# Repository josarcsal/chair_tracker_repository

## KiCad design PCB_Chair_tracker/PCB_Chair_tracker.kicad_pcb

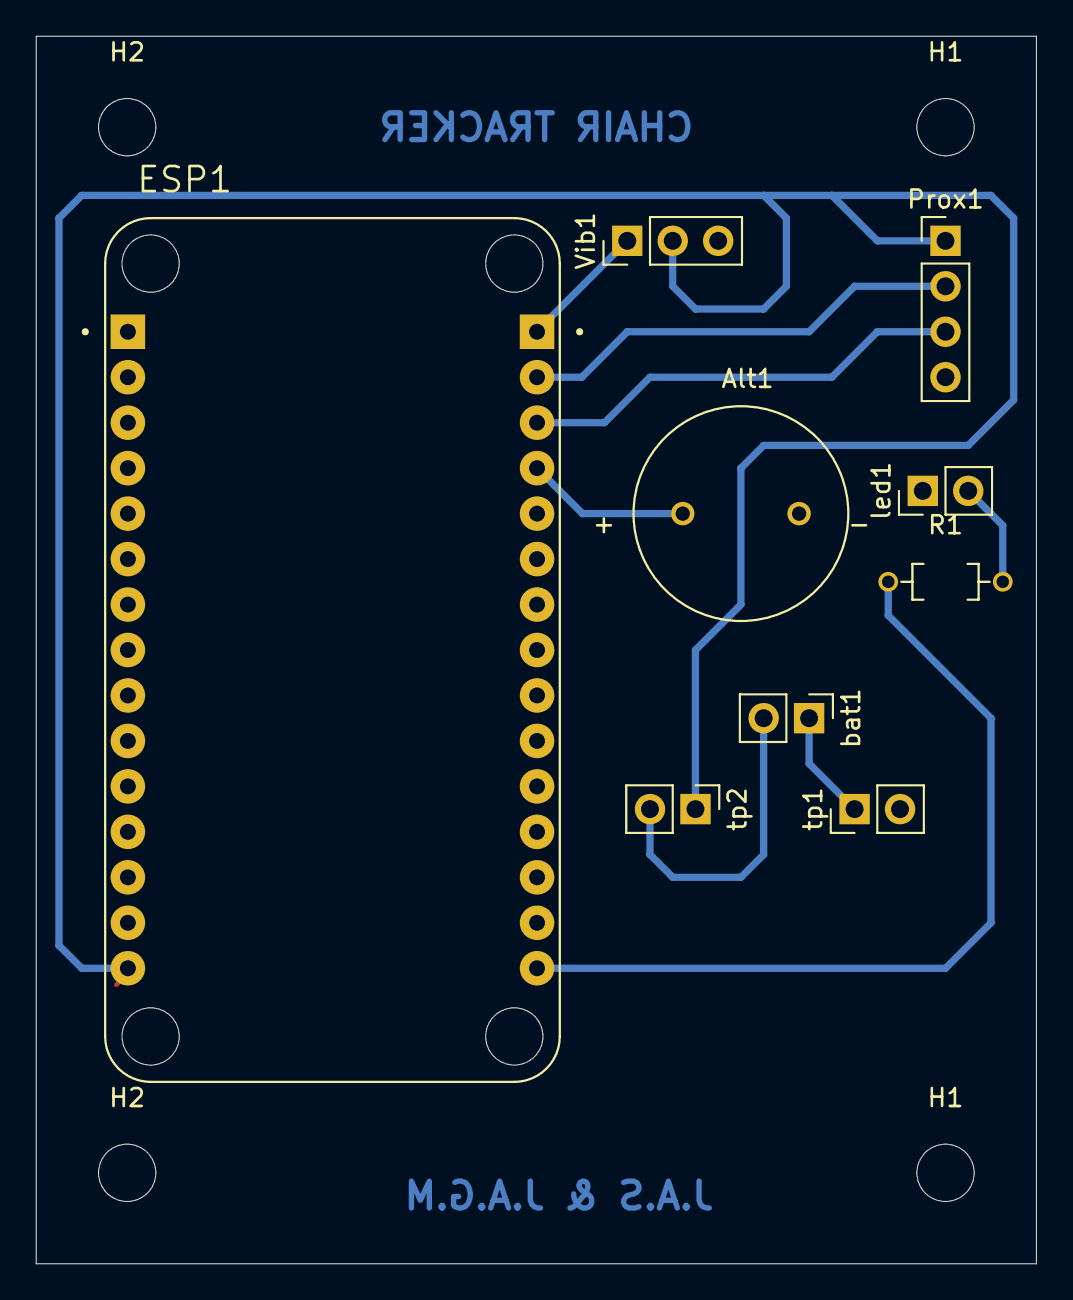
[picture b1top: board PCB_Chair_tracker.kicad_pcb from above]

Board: 2 copper layers, 55.9 x 68.6 mm, 13 parts (0 on the bottom side), 10 nets.

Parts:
Alt1: CEM-1203(42); CUI_CEM-1203(42)
ESP1: 113990105; SEEED_113990105
H1, H1#2, H2, H2#2: MountingHole; MountingHole_3.2mm_M3
Prox1: Conn_01x04_Male; PinHeader_1x04_P2.54mm_Vertical
R1: 1614977-1; RESAD640W45L370D200
Vib1: Conn_01x03_Male; PinHeader_1x03_P2.54mm_Vertical
bat1: Conn_01x02_Male; PinHeader_1x02_P2.54mm_Vertical
led1: Conn_01x02_Male; PinHeader_1x02_P2.54mm_Vertical
tp1, tp2: Conn_01x02_Male; PinHeader_1x02_P2.54mm_Vertical

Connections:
/3V3: ESP1.J2_15, R1.1
/ALARMA_PIN: Alt1.P, ESP1.J2_4
/B+: bat1.2, tp2.2
/B-: bat1.1, tp1.1
/ECHO_PIN: ESP1.J2_3, Prox1.3
/GND: Alt1.N, ESP1.J2_14, Prox1.4, Vib1.3, led1.1, tp1.2
/TRIGGER_PIN: ESP1.J2_2, Prox1.2
/VIBRADOR_PIN: ESP1.J2_1, Vib1.1
/VIN: ESP1.J1_15, Prox1.1, Vib1.2, tp2.1
unnamed: R1.2, led1.2

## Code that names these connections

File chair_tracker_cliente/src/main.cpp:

#include <Arduino.h>
#include <PubSubClient.h>
#include <Ethernet.h>
#include <ESP8266WiFi.h>
#include <ArduinoHttpClient.h>
#include <ArduinoJson.h>
#include <NewPing.h>
#include <ListLib.h>
#include <NTPClient.h>
#include "WiFiUdp.h"
#include <TimeLib.h>

#include "request.h"
#include "Hash.h"
#include "alarma.h"

#include "WiFiManager.h"      
#include <DNSServer.h>
#include <ESP8266WebServer.h>
#include <WiFiManager.h>        

//Obtener hora
WiFiUDP ntpUDP;
NTPClient timeClient(ntpUDP, "europe.pool.ntp.org", 7200);

//Sensor proximidad
#define TRIGGER_PIN D1
#define ECHO_PIN D2
#define MAX_DISTANCE 200 // Distancia máxima

NewPing sonar(TRIGGER_PIN, ECHO_PIN, MAX_DISTANCE);

//Alarma y vibrador
#define ALARMA_PIN D3
#define VIBRADOR_PIN D0

//Funciones mqtt
void callback(char *topic, byte *payload, unsigned int length);
void reconnect();

//Wifi
WiFiManager wm;
char server[40] = "0.0.0.0";
char http_port[6]  = "8084";
char mqtt_port[6]  = "1883";
WiFiManagerParameter custom_server("server", "Server IP", server, 40);
WiFiManagerParameter custom_http_port("http_port", "API Port", http_port, 6);
WiFiManagerParameter custom_mqtt_port("mqtt_port", "MQTT Port", mqtt_port, 6);

const char *mqttUser = "root";
const char *mqttPassword = "root";

WiFiClient espClient;
PubSubClient mqttClient(espClient);
HttpClient httpClient = HttpClient(espClient, server, atoi(http_port));

//Obtiene mac y realiza hash con algoritmo sha1 para mayor seguridad
String macEsp = sha1(WiFi.macAddress());
String hashMac = macEsp.substring(0,10);

//Gestion alarmas
String proxima;
int wifiFlag = 0;
int alarmaActiva = 0;
int inicioAlarma = 0;
int distanciaAnterior = 50;
int levantado = 10;
int marcaTiempo1;
int marcaTiempo2;
int contadorLevantado;
int contadorSentado;
int ciclosTrabajo;
int ciclosDescanso;

void setup()
{
  Serial.begin(9600);

  wm.resetSettings();
  
  //WIFI
  delay(3000);
  // Serial.println("Setup mode...");
  //wifiManager.resetSettings();
 
  wm.addParameter(&custom_server);
  wm.addParameter(&custom_mqtt_port);
  wm.addParameter(&custom_http_port);

  wm.setConfigPortalBlocking(false);

  if(wm.autoConnect("ChairTrackerAP"))
  {
    //if you get here you have connected to the WiFi
    Serial.println("connected...yeey :)");
  }
  else 
  {
    Serial.println("non blocking config portal running");
  }
  wm.startConfigPortal("ChairTrackerAP");

  Serial.print("Hash MAC: ");
  Serial.println(hashMac);
  
  //Alarma y vibrador
  pinMode(ALARMA_PIN, OUTPUT);
  pinMode(VIBRADOR_PIN, OUTPUT);
}

void loop()
{
  wm.process();
  if(WiFi.isConnected()){
    strcpy(server, custom_server.getValue());
    strcpy(http_port, custom_http_port.getValue());
    strcpy(mqtt_port, custom_mqtt_port.getValue());

    if(wifiFlag == 0){ 
      //MQTT
      mqttClient.setServer(server, atoi(mqtt_port));
      mqttClient.setCallback(callback);
      delay(100);
      
      //TIEMPO
      timeClient.begin();
      String lista = obtenerListaHoras(httpClient, hashMac);
      Serial.println(lista);
      proxima = obtenerProximaAlarma(httpClient, timeClient, hashMac);
      Serial.print("La proxima alarma es ");
      Serial.println(proxima);

      wifiFlag = 1;
    }

    timeClient.update();
    marcaTiempo1 = timeClient.getHours() * 3600 + timeClient.getMinutes() * 60 + timeClient.getSeconds();
    
    //MQTT
    if (!mqttClient.connected())
    {
      reconnect();
    }
    mqttClient.loop();

    delay(3000);

    //SENSOR
    int distanciaActual = sonar.ping_cm();
    Serial.print("Distancia actual: ");
    Serial.println(distanciaActual);

    //ALARMA
    int proximaT_inicio = StringToIntAlarma(proxima, "t_inicio");
    int proximaT_final = StringToIntAlarma(proxima, "t_final");
    int proximaT_trabajo = StringToIntAlarma(proxima, "t_trabajo");
    int proximaT_descanso = StringToIntAlarma(proxima, "t_descanso");
    int proximaOid = StringToIntAlarma(proxima, "oid_alarma");
    int proximaCiclosTrabajo = StringToIntAlarma(proxima, "ciclos_trabajo");
    int proximaCiclosDescanso = StringToIntAlarma(proxima, "ciclos_descanso");

    if (marcaTiempo1 >= proximaT_inicio && marcaTiempo1 <= proximaT_final)
    {
      alarmaActiva = 1;
      if(inicioAlarma == 0){
        inicioAlarma = 1;
        onOffAlarma(ALARMA_PIN);
      }
      if (distanciaActual < 20 && distanciaAnterior > 40)
      {
        Serial.println("Me siento");
        levantado = 0;
      }

      if (distanciaAnterior < 20 && distanciaActual > 40)
      {
        Serial.println("Me levanto");
        levantado = 1;
      }

      distanciaAnterior = distanciaActual;

      marcaTiempo2 = timeClient.getHours() * 3600 + timeClient.getMinutes() * 60 + timeClient.getSeconds();

      if (levantado == 0)
      {
        contadorSentado += marcaTiempo2 - marcaTiempo1;
      }

      if (levantado == 1)
      {
        contadorLevantado += marcaTiempo2 - marcaTiempo1;
      }

      if (contadorSentado > (proximaT_trabajo * 60))
      {
        contadorSentado = 0;
        ciclosTrabajo += 1;
        Serial.println("Alarma sonando es tiempo de descansar");
        sonarAlarma(ALARMA_PIN);
      }

      if (contadorLevantado > (proximaT_descanso * 60))
      {
        contadorLevantado = 0;
        ciclosDescanso += 1;
        Serial.println("Alarma sonando es tiempo de trabajar");
        sonarAlarma(ALARMA_PIN);
      }
    }
    else
    {
      if (proxima != "No se ha encontrado alarma para el dia de hoy" && marcaTiempo1 > proximaT_final)
      {
        int ciclosTUpdate = proximaCiclosTrabajo + ciclosTrabajo;
        int ciclosDUpdate = proximaCiclosDescanso + ciclosDescanso;

        String t_inicioFormateado = timeFromClientToBBDD(getValue(proxima, '|', 0));
        String t_finFormateado = timeFromClientToBBDD(getValue(proxima, '|', 1));

        DynamicJsonDocument bodyPut(1024);
        String bodyPutData = "";
        bodyPut[String("oid_alarma")] = String(proximaOid);
        bodyPut[String("dias")] = String(getValue(proxima, '|', 2));
        bodyPut[String("t_inicio")] = String(t_inicioFormateado);
        bodyPut[String("t_fin")] = String(t_finFormateado);
        bodyPut[String("t_trabajo")] = String(proximaT_trabajo);
        bodyPut[String("t_descanso")] = String(proximaT_descanso);
        bodyPut[String("ciclo_trabajo")] = String(ciclosTUpdate);
        bodyPut[String("ciclo_descanso")] = String(ciclosDUpdate);
        bodyPut[String("hash_mac_fk")] = String(hashMac);

        serializeJson(bodyPut, bodyPutData);

        doRequest(httpClient, "PUT", "/api/alarmas/editarAlarma", bodyPutData);

        proxima = obtenerProximaAlarma(httpClient, timeClient, hashMac);
        Serial.println("Actualizada alarma siguiente");
        Serial.print("Nuevo inicio ");
        Serial.println(StringToIntAlarma(proxima, "t_inicio"));
        Serial.print("Nuevo final ");
        Serial.println(StringToIntAlarma(proxima, "t_final"));
      }

      distanciaAnterior = 50;
      levantado = 10;
      contadorLevantado = 0;
      contadorSentado = 0;
      ciclosTrabajo = 0;
      ciclosDescanso = 0;
      alarmaActiva = 0;
      if(inicioAlarma == 1){
        inicioAlarma = 0;
        onOffAlarma(ALARMA_PIN);
      }
    }
  } 
}

//------------------------------------------------------------------------------------------------------
//Metodos MQTT
void callback(char *topic, byte *payload, unsigned int length)
{
  Serial.print("Message arrived [");
  Serial.print(topic);
  Serial.print("] ");
  for (unsigned int i = 0; i < length; i++)
  {
    Serial.print((char)payload[i]);
  }
  Serial.println();

  String topicCmp1 = hashMac + "/llamadas/recibidas";
  String topicCmp2 = hashMac + "/alarmas/refresh";

  int topicLlamada = strcmp(topic, topicCmp1.c_str());
  int topicAlarma = strcmp(topic, topicCmp2.c_str());

  if (topicLlamada == 0)
  {
    //ENCENDER ALARMA POR LLAMADA
    Serial.println("Estan llamando");
    sonarVibrador(VIBRADOR_PIN);
  }

  if ((topicAlarma == 0) && (alarmaActiva == 0))
  {
    proxima = obtenerProximaAlarma(httpClient, timeClient, hashMac);
    Serial.print("Se han actualizado las alarmas y la proxima es ");
    Serial.println(proxima);
  }
}

void reconnect()
{
  // Loop until we're reconnected
  while (!mqttClient.connected())
  {
    Serial.print("Attempting MQTT connection...");
    // Attempt to connect
    if (mqttClient.connect("ESP8266Client", mqttUser, mqttPassword))
    {
      Serial.println("connected");
      // ... and resubscribe
      String topic1 = hashMac + "/#";
      mqttClient.subscribe(topic1.c_str());
    }
    else
    {
      Serial.print("failed, rc=");
      Serial.print(mqttClient.state());
      Serial.println(" try again in 5 seconds");
      // Wait 5 seconds before retrying
      delay(5000);
    }
  }
}

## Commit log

2021-05-04 Primer entregable
    Realizada la parte correspondiente al servidor
2021-05-04 Solucionado error get llamada
2021-05-04 Añadido gitignore pom.properties
2021-05-04 Añadido comprobacion COUNT antes de ediciones y eliminaciones
2021-05-04 Añadido parametros al gitignore
2021-05-09 Clase MQTT creada
2021-05-10 Iniciacion de cliente mqtt
2021-05-10 Cambio de libreria
2021-05-10 Comienzo de control de errores servers
2021-05-10 Envio de datos por body
2021-05-15 Peticiones desde cliente
    Cambios del cliente para realizar todo tipo de peticiones ademas de unificarlo todo en una unica clase.
    Modificiones del servidor para su correcto funcionamiento.
    Debemos añadir comprobaciones en el server para los parametros de los edits y testear todos los metodos de nuevo desde el postman usando el body en lugar de cabecera
2021-05-16 Cambios URL y Query llamadas
2021-05-17 Principio mqtt cliente
2021-05-17 Añadido mac a base de datos
    Cambio en tablas, tiggers e inserts para acomodar al parametro mac como pk y fk
2021-05-17 Modificacion servidor hash_mac
2021-05-17 Cambio httpVerticle para hash_mac
2021-05-17 Eliminacion placa
2021-05-17 Cambios server hash
2021-05-17 Arreglos cliente mqtt, server mqtt
2021-05-18 Mqqt cliente añadido al main
2021-05-18 Cliente mqtt vertx
2021-05-19 Implementado sensor de proximidad
    Normalizar las señales de tierra al usar fuente externa en montaje
2021-05-20 Conexion vertx mqtt
    Iniciado cliente mediante paso de mensajes en servidor
2021-05-20 Mqtt de llamadas casi terminado
2021-05-20 Llamada mqtt casi lista
2021-05-20 Comentario de posible implementacion alarmas
2021-05-21 Intento de implementacion alarmas en cliente
2021-05-21 Parametros red movil
2021-05-21 Recogida de alarmas en cliente
2021-05-21 Control de alarmas del dia
2021-05-22 Regla de negocio alarmas
2021-05-22 Inicio contador tiempo alarma
2021-05-22 Continuacion contador
2021-05-22 Version funcional del contador
2021-05-22 Cambio http alarmas
2021-05-22 Cambios en la BBDD para implementacion de triggers y ciclos_trabajo/ciclos_descanso
2021-05-22 Continuo contador
2021-05-23 Apuesta alarmas
2021-05-23 Terminado contador y suscripciones mqtt
2021-05-24 Primera version del segundo entregable
2021-05-24 Correcion sql
2021-06-06 Cambio en los pines del monaje y eliminacion de trigger fallido
2021-06-08 Añadida documentacion
2022-02-28 chore: change project structure and do first mockup
2022-02-28 refactor: change app colors
2022-02-28 chore: add icons and fix some views
2022-03-01 fix: fix header safeTop
2022-03-19 feat: add axios connection and use first queries
2022-03-19 fix: fix numColumns in alarm screen
2022-03-20 chore: refactor normalizations for alarms and contacts
2022-03-21 feat: add params queries to be able to use axios
2022-03-21 feat: login frontend
2022-03-22 feat: add alarm queries
2022-03-22 feat:add alarm queries
2022-03-23 feat: forms
2022-04-08 chore: new libraries
2022-04-09 feat: inputs and stadistics
2022-04-09 feat: add non blocking wifimanager to client
2022-04-10 feat: add hashMac to borrarAlarma and refactor code
2022-04-10 chore: changed margins
2022-04-10 chore: change whole app theme
2022-04-14 fix: change margins and wip trigger modification
2022-04-20 chore: change welcome-colors
2022-04-20 feat: tab-page-calls
2022-04-22 feat: add calendar to profile screen
2022-04-23 try: add calendar style
2022-04-23 feat: check-user-exist and some api hooks
2022-04-24 feat: call card
2022-04-24 chore: add alarms style
2022-04-24 chore: update poms
2022-04-24 feat: useregistroalarmas and fixes in api
2022-04-24 fix: change gitignore
2022-04-27 feat: login and add alarm
2022-04-27 fix: solve api post alarm errors
2022-05-01 feat: db and api changes with new methods
2022-05-01 fix: minor fix in mac 10 chars
2022-05-01 feat: backend data connection
2022-05-01 feat: welcome image and form register changes
2022-05-02 chore: feat register, terms and conditions
2022-05-02 feat: create modals and implement delete alarm
2022-05-03 feat: add alarm
2022-05-03 feat: call a contact
2022-05-03 fix: time error and axios hooks
2022-05-03 chore: add data call history and minor bug fixes
2022-05-03 fix: delete comments
2022-05-04 feat: new alarms from boss
2022-05-04 feat: calendar-function
2022-05-04 feat: validation in forms
2022-05-04 chore: changes in style
2022-05-04 fix: delete node_modules
2022-05-05 fix: picker style for iOS
2022-05-05 feat: backend initial state
2022-05-06 fix: welcome spaces for iOS
2022-05-06 fix: internal bugs
2022-05-06 sh: q: command not found
2022-05-06 fix: control errors in api and refactor trigger
2022-05-06 fix: header-for-small-devices
2022-05-07 wip: mqtt
2022-05-07 fix: connection
2022-05-07 feat: mqtt now connects correctly
2022-05-11 feat: add on off sound when an alarm start or finish
2022-05-11 refactor: change db name
2022-05-15 feat: add rn-mqtt-client and add one new method to api
2022-05-15 feat: add api method to get all user alarm registry given a year
2022-05-15 fix: delete old files
2022-05-21 chore: ordered registers
2022-07-16 chore: add pcb and 3d desgin
2022-07-16 chore: add mosquitto.conf
